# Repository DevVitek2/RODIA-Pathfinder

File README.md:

# RODIA Pathfinder

<p align="center"><i>AI-generated visualisation of the PCB2.3 board: front (left) and back (right).</i></p>

**RODIA Pathfinder** is the first iteration of a custom RP2040 flight computer for
**Trinity**, the hybrid rocket-drone vehicle of the student team Manhattan Rockets
(Czech Rocket Society). It is a 40 × 40 mm, two-layer board designed in KiCad and
manufactured and assembled by JLCPCB.

Pathfinder is not meant to fly. It exists to prove the core of the design in hardware
(MCU, power, flash, barometer, pyro channel) before the more demanding
**RODIA** (*Rocket Onboard Drone Interface Avionics*) board is built.

Full documentation (Czech, 19 pages): [`MR_PCB2_DOCUM_FINAL.pdf`](MR_PCB2_DOCUM_FINAL.pdf)

## Board overview

| Parameter | Value |
|---|---|
| MCU | RP2040 (dual Cortex-M0+, no FPU) |
| Flash | W25Q128JVS, 16 MB, QSPI (firmware + sensor data) |
| Sensor | BMP388 barometer (I2C, address `0x76`) |
| Power | USB-C (5 V) or Li-Po 2S–3S via XT30, Schottky OR-ing + TVS protection on both inputs |
| Logic | 3.3 V, NCP1117-3.3 linear regulator |
| Pyro channel | AO3400A MOSFET, powered directly from the battery, XT30 output (J5) |
| Size | 40 × 40 mm, 1.6 mm, 2 layers, 3 × 2.5 mm mounting holes |
| Expansion | J3 (2 × 9) and J4 (1 × 9) pin headers, 2.54 mm, for stacking boards |

| 3D view, top | 3D view, bottom |
|---|---|
|  |  |

Full schematic: [`images/schematic.pdf`](images/schematic.pdf)

## Status

**Verified on hardware**
- Power from USB-C and from a 2S battery
- Firmware upload over USB (BOOT button, mass-storage mode)
- BMP388 barometer: 25 Hz logging, ±0.1 m noise
- BNO085 orientation sensor (on the extension board) sharing the I2C bus with the BMP388

**Known issues** (input for the next revision)
- J3 silkscreen GPIO labels are shifted by two (see [`rodia-pathfinder/AVIONICS.md`](rodia-pathfinder/AVIONICS.md))
- No SWD pads, so no hardware debugging
- Linear regulator dissipates ~0.9 W from a full 3S pack at 100 mA; a switching regulator would remove this
- SD card module on the extension board needs 5 V, which is not available in flight
- No flyback diode on the pyro channel: fine for a resistive e-match, not for inductive loads

## Repository structure

```
.
├── README.md
├── MR_PCB2_DOCUM_FINAL.pdf                 full Pathfinder documentation (Czech)
├── images/                                 renders, schematic blocks, copper layers
├── rodia-pathfinder/                       design files
│   ├── AVIONICS.md                         pin map, SPI rules, firmware build, hardware status
│   ├── PCB2.3_JF/                          main board: KiCad project + JLCPCB production files
│   ├── Sensor_board_1.2/                   extension board: BNO085, SD card, LEDs, buzzer
│   └── datasheets+components+min-design/   datasheets, component lists, RP2040 minimal reference design
└── rodia/                                  the next board
    ├── RODIA_project_brief_EN.pdf          motivation, idea, requirements
    └── RODIA_block_diagram.pdf / .odg      simplified system diagram
```

## What comes next: RODIA

Trinity flies a ballistic rocket ascent followed by a powered, controlled drone descent.
The drone flight controller handles the descent, but its firmware only provides filtered data
tuned for propeller flight, and its accelerometer is close to its range limit under rocket loads.
RODIA is a second, independent flight computer that connects to the drone flight controller,
follows drone-FC mechanical standards, logs raw sensor data, talks to the ground station
and can carry out the critical functions (parachute deployment) on its own if the drone FC
fails. See [`rodia/RODIA_project_brief_EN.pdf`](rodia/RODIA_project_brief_EN.pdf).

## About

Designed by **Vít Krejčí** (avionics, Manhattan Rockets, a student rocketry team operating
under the Czech Rocket Society).

Datasheets in `rodia-pathfinder/datasheets+components+min-design/` belong to their respective
manufacturers and are included for reference only.

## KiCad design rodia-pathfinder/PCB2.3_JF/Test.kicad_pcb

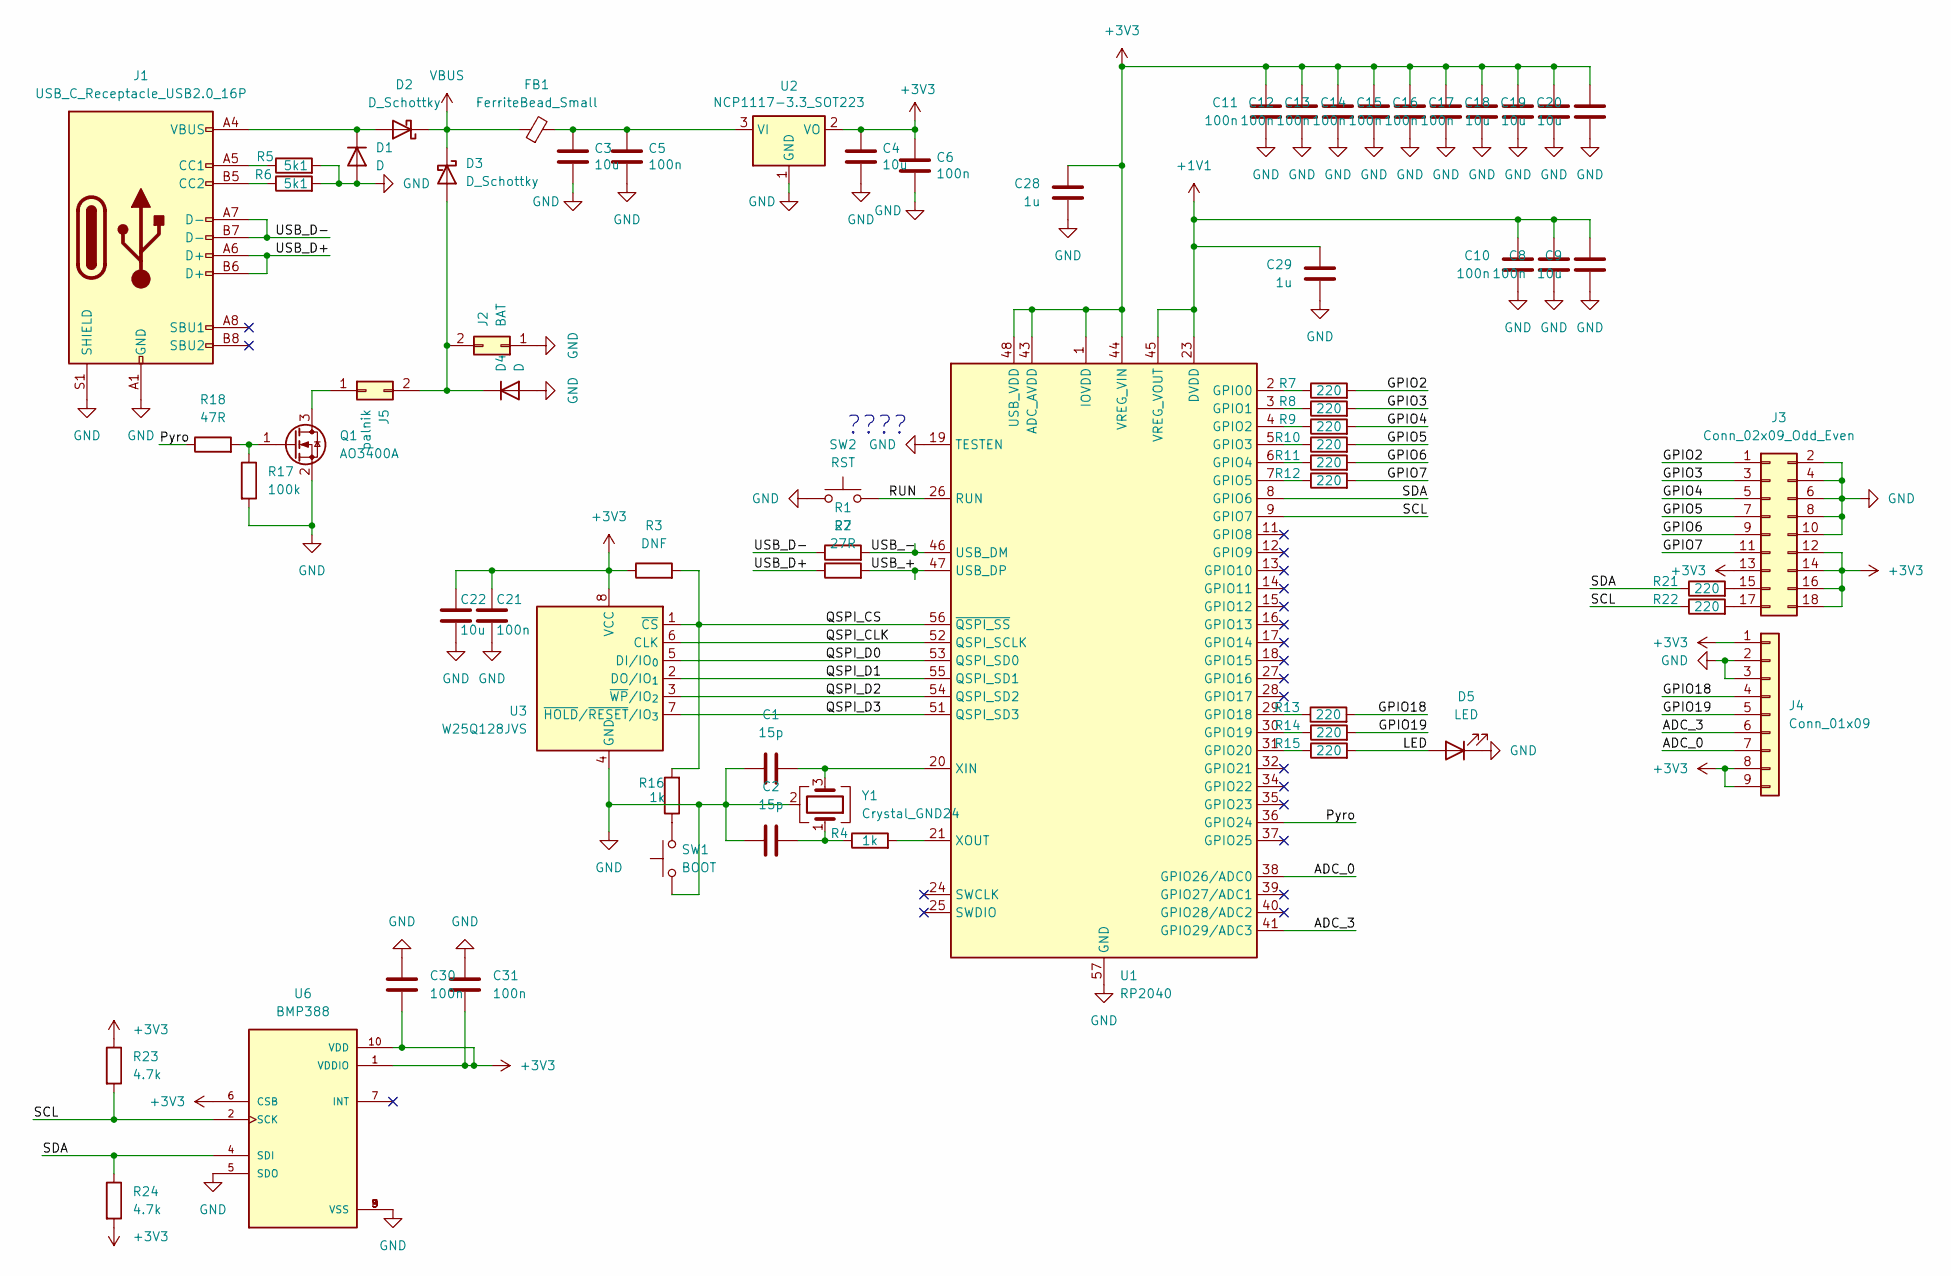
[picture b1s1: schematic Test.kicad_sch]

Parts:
C1, C2: 15p; C_0402_1005Metric
C3, C4, C9, C18, C19, C20, C22: 10u; C_0402_1005Metric
C5, C6, C8, C10, C11, C12, C13, C14, C15, C16, C17, C21, C30, C31: 100n; C_0402_1005Metric
C28, C29: 1u; C_0402_1005Metric
D1, D4: D; D_SMB
D2, D3: D_Schottky; D_SMA
D5: LED; LED_0805_2012Metric
FB1: FerriteBead_Small; R_0805_2012Metric
J1: USB_C_Receptacle_USB2.0_16P; USB_C_Receptacle_HCTL_HC-TYPE-C-16P-01A
J2: BAT; AMASS_XT30UPB-M_1x02_P5.0mm_Vertical
J3: Conn_02x09_Odd_Even; PinSocket_2x09_P2.54mm_Vertical
J4: Conn_01x09; PinSocket_1x09_P2.54mm_Vertical
J5: palnik; AMASS_XT30UPB-M_1x02_P5.0mm_Vertical
Q1: AO3400A; SOT-23
R1: 27; R_0402_1005Metric
R2: 27R; R_0402_1005Metric
R3: DNF; R_0603_1608Metric
R4, R16: 1k; R_0402_1005Metric
R5, R6: 5k1; R_0603_1608Metric
R7, R8, R9, R10, R11, R12, R13, R14, R15, R21, R22: 220; R_0603_1608Metric
R17: 100k; R_0603_1608Metric
R18: 47R; R_0603_1608Metric
R23, R24: 4.7k; R_0603_1608Metric
SW1: BOOT; SW_Push_1P1T-SH_NO_CK_KMR2xxG
SW2: RST; SW_Push_1P1T-SH_NO_CK_KMR2xxG
U1: RP2040; QFN-56-1EP_7x7mm_P0.4mm_EP3.2x3.2mm_ThermalVias
U2: NCP1117-3.3_SOT223; SOT-223-3_TabPin2
U3: W25Q128JVS; SOIC-8_5.3x5.3mm_P1.27mm
U6: BMP388; PQFN50P200X200X80-10N; PARTREV 1.1
Y1: Crystal_GND24; Crystal_SMD_3225-4Pin_3.2x2.5mm

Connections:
+1V1: C8.1, C9.1, C10.1, C29.1, U1.23 (DVDD), U1.45 (VREG_VOUT), U1.50 (DVDD)
+3V3: C4.1, C6.1, C11.1, C12.1, C13.1, C14.1, C15.1, C16.1, C17.1, C18.1, C19.1, C20.1, C21.1, C22.1, C28.1, C30.2, C31.2, J3.12, J3.13, J3.14, J3.16, J3.18, J4.1, J4.8, J4.9, R3.1, R23.1, R24.2, U1.1 (IOVDD), U1.10 (IOVDD), U1.22 (IOVDD), U1.33 (IOVDD), U1.42 (IOVDD), U1.43 (ADC_AVDD), U1.44 (VREG_VIN), U1.48 (USB_VDD), U1.49 (IOVDD), U2.2 (VO), U3.8 (VCC), U6.1 (VDDIO), U6.6 (CSB), U6.10 (VDD)
/ADC_0: J4.7, U1.38 (GPIO26/ADC0)
/ADC_3: J4.6, U1.41 (GPIO29/ADC3)
/GPIO2: J3.1, R7.2
/GPIO3: J3.3, R8.2
/GPIO4: J3.5, R9.2
/GPIO5: J3.7, R10.2
/GPIO6: J3.9, R11.2
/GPIO7: J3.11, R12.2
/GPIO18: J4.4, R13.2
/GPIO19: J4.5, R14.2
/LED: D5.2 (A), R15.2
/Pyro: R18.1, U1.36 (GPIO24)
/QSPI_CLK: U1.52 (QSPI_SCLK), U3.6 (CLK)
/QSPI_CS: R3.2, R16.2, U1.56 (~QSPI_SS), U3.1 (~CS)
/QSPI_D0: U1.53 (QSPI_SD0), U3.5 (DI/IO_{0})
/QSPI_D1: U1.55 (QSPI_SD1), U3.2 (DO/IO_{1})
/QSPI_D2: U1.54 (QSPI_SD2), U3.3 (~WP/IO_{2})
/QSPI_D3: U1.51 (QSPI_SD3), U3.7 (~HOLD/~RESET/IO_{3})
/RUN: SW2.1, U1.26 (RUN)
/SCL: R22.1, R23.2, U1.9 (GPIO7), U6.2 (SCK)
/SDA: R21.1, R24.1, U1.8 (GPIO6), U6.4 (SDI)
/USB_+: R2.2, U1.47 (USB_DP)
/USB_-: R1.2, U1.46 (USB_DM)
/USB_D+: J1.A6 (D+), J1.B6 (D+), R2.1
/USB_D-: J1.A7 (D-), J1.B7 (D-), R1.1
GND: C1.1, C2.1, C3.2, C4.2, C5.2, C6.2, C8.2, C9.2, C10.2, C11.2, C12.2, C13.2, C14.2, C15.2, C16.2, C17.2, C18.2, C19.2, C20.2, C21.2, C22.2, C28.2, C29.2, C30.1, C31.1, D1.2 (A), D4.2 (A), D5.1 (K), J1.A1 (GND), J1.A12 (GND), J1.B1 (GND), J1.B12 (GND), J1.S1 (SHIELD), J2.1, J3.2, J3.4, J3.6, J3.8, J3.10, J4.2, J4.3, Q1.2 (S), R5.2, R6.2, R17.2, SW1.1, SW2.2, U1.19 (TESTEN), U1.57 (GND), U2.1 (GND), U3.4 (GND), U6.3 (VSS), U6.5 (SDO), U6.8 (VSS), U6.9 (VSS), Y1.2 (G), Y1.4 (G)
unnamed: C2.2, R4.1, Y1.1
unnamed: D1.1 (K), D2.2 (A), J1.A4 (VBUS), J1.A9 (VBUS), J1.B4 (VBUS), J1.B9 (VBUS)
unnamed: D3.2 (A), D4.1 (K), J2.2, J5.2
unnamed: J1.A5 (CC1), R5.1
unnamed: J1.B5 (CC2), R6.1
unnamed: J3.15, R21.2
unnamed: J3.17, R22.2
unnamed: J5.1, Q1.3 (D)
unnamed: Q1.1 (G), R17.1, R18.2
unnamed: R16.1, SW1.2
unnamed: R7.1, U1.2 (GPIO0)
unnamed: R8.1, U1.3 (GPIO1)
unnamed: R9.1, U1.4 (GPIO2)
unnamed: R10.1, U1.5 (GPIO3)
unnamed: R11.1, U1.6 (GPIO4)
unnamed: R12.1, U1.7 (GPIO5)
unnamed: R13.1, U1.29 (GPIO18)
unnamed: R14.1, U1.30 (GPIO19)
unnamed: R15.1, U1.31 (GPIO20)
unnamed: C1.2, U1.20 (XIN), Y1.3
unnamed: R4.2, U1.21 (XOUT)
unnamed: C3.1, C5.1, FB1.2, U2.3 (VI)
VBUS: D2.1 (K), D3.1 (K), FB1.1

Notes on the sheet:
????

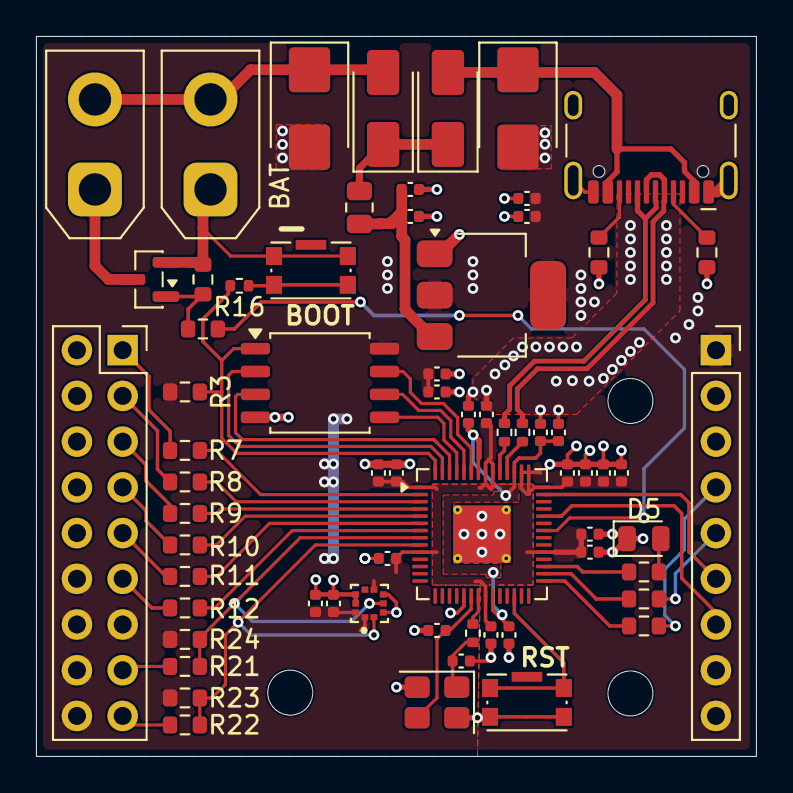
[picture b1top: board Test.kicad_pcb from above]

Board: 2 copper layers, 40.0 x 40.0 mm, 66 parts (0 on the bottom side), 51 nets.

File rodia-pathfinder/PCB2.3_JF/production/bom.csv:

Designator,Footprint,Quantity,Value,LCSC Part #
"C1, C2",0402,2,15p,
"C10, C11, C12, C13, C14, C15, C16, C17, C21, C30, C31, C5, C6, C8",0402,14,100n,
"C18, C19, C20, C22, C3, C4, C9",0402,7,10u,
"C28, C29",0402,2,1u,
"D1, D4",D_SMB,2,D,
"D2, D3",D_SMA,2,D_Schottky,
D5,0805,1,LED,
FB1,0805,1,FerriteBead_Small,
J1,USB_C_Receptacle_HCTL_HC-TYPE-C-16P-01A,1,USB_C_Receptacle_USB2.0_16P,
J2,AMASS_XT30UPB-M_1x02_P5.0mm_Vertical,1,BAT,
J3,PinSocket_2x09_P2.54mm_Vertical,1,Conn_02x09_Odd_Even,
J4,PinSocket_1x09_P2.54mm_Vertical,1,Conn_01x09,
J5,AMASS_XT30UPB-M_1x02_P5.0mm_Vertical,1,palnik,
Q1,SOT-23,1,AO3400A,
R1,0402,1,27,
"R10, R11, R12, R13, R14, R15, R21, R22, R7, R8, R9",0603,11,220,
"R16, R4",0402,2,1k,
R17,0603,1,100k,
R18,0603,1,47R,
R2,0402,1,27R,
"R23, R24",0603,2,4.7k,
R3,0603,1,DNF,
"R5, R6",0603,2,5k1,
SW1,SW_Push_1P1T-SH_NO_CK_KMR2xxG,1,BOOT,
SW2,SW_Push_1P1T-SH_NO_CK_KMR2xxG,1,RST,
U1,QFN-56-1EP_7x7mm_P0.4mm_EP3.2x3.2mm_ThermalVias,1,RP2040,
U2,SOT-223-3_TabPin2,1,NCP1117-3.3_SOT223,
U3,SOIC-8_5.3x5.3mm_P1.27mm,1,W25Q128JVS,
U6,PQFN50P200X200X80-10N,1,BMP388,
Y1,Crystal_SMD_3225-4Pin_3.2x2.5mm,1,Crystal_GND24,

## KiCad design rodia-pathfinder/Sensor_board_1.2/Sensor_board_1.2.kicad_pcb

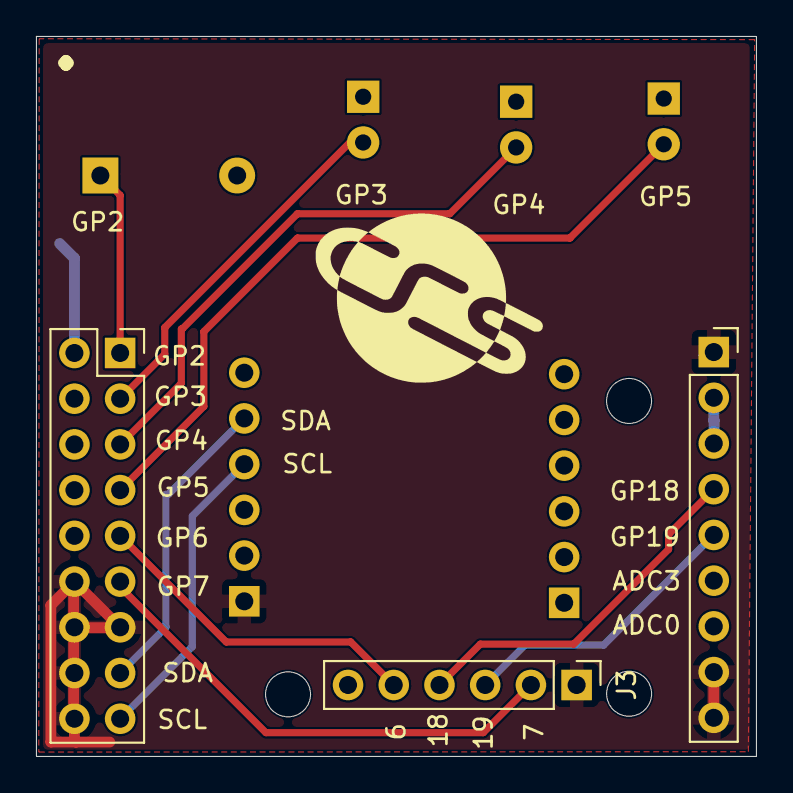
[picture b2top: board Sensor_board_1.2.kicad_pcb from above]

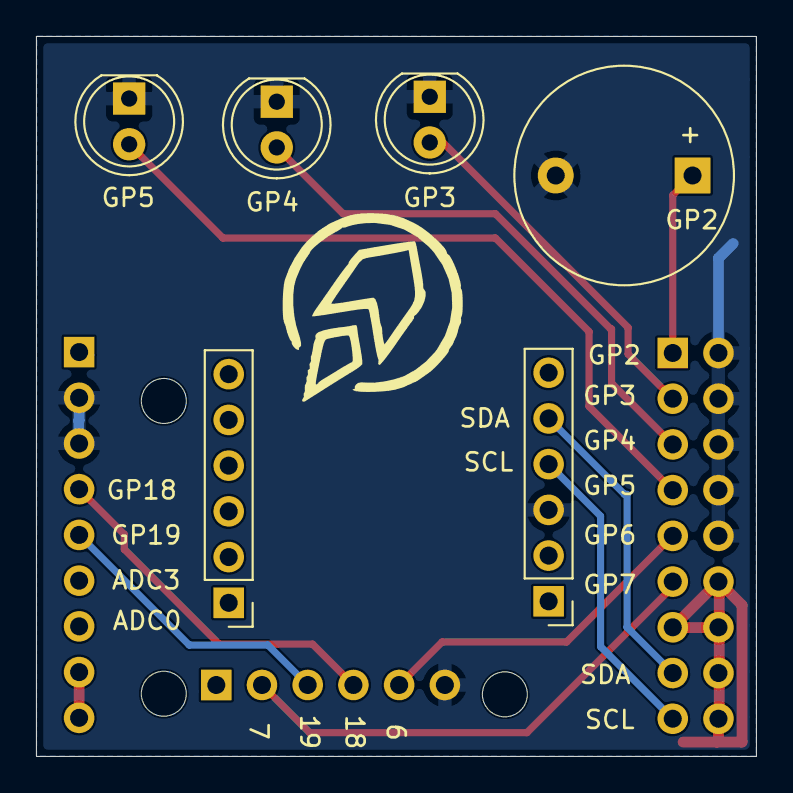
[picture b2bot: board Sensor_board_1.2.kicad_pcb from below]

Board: 2 copper layers, 40.0 x 40.0 mm, 9 parts (5 on the bottom side), 12 nets.

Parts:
BZ1: Buzzer; Buzzer_12x9.5RM7.6
D1, D2, D3: LED; LED_D5.0mm
J1, J2, J3: Conn_01x06; PinSocket_1x06_P2.54mm_Vertical
J5: Conn_02x09_Odd_Even; PinSocket_2x09_P2.54mm_Vertical
J6: Conn_01x09; PinSocket_1x09_P2.54mm_Vertical

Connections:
+3V3: J2.1, J3.1, J5.12, J5.13, J5.14, J5.16, J5.18, J6.1, J6.8, J6.9
/GPIO2: BZ1.1 (+), J5.1
/GPIO3: D2.2 (A), J5.3
/GPIO4: D1.2 (A), J5.5
/GPIO5: D3.2 (A), J5.7
/GPIO6: J3.5, J5.9
/GPIO7: J3.2, J5.11
/GPIO18: J3.4, J6.4
/GPIO19: J3.3, J6.5
/SCL: J2.4, J5.17
/SDA: J2.5, J5.15
GND: BZ1.2 (-), D1.1 (K), D2.1 (K), D3.1 (K), J2.3, J3.6, J5.2, J5.4, J5.6, J5.8, J5.10, J6.2, J6.3

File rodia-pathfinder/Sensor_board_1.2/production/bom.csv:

Designator,Footprint,Quantity,Value,LCSC Part #
"_3, _2, ",,3,,
BZ1,Buzzer_12x9.5RM7.6,1,Buzzer,
"D1, D2, D3",LED_D5.0mm,3,LED,
"J1, J2, J3",PinSocket_1x06_P2.54mm_Vertical,3,Conn_01x06,
J5,PinSocket_2x09_P2.54mm_Vertical,1,Conn_02x09_Odd_Even,
J6,PinSocket_1x09_P2.54mm_Vertical,1,Conn_01x09,
